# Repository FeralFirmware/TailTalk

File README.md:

# TailTalk

[![Crates.io][crates-badge]][crates-url] [![docs.rs][docs-badge]][docs-url]

[crates-badge]: https://img.shields.io/crates/v/tailtalk.svg
[crates-url]: https://crates.io/crates/tailtalk
[docs-badge]: https://img.shields.io/docsrs/tailtalk.svg
[docs-url]: https://docs.rs/tailtalk/latest/tailtalk/

TailTalk is designed as a "toolkit" for building fully userspace AppleTalk implementations on Linux, Mac OS and Windows
systems via EtherTalk or LocalTalk networks. It is built from scratch with zero dependencies on Netatalk or any kernel
drivers - All it needs is a raw socket and/or TashTalk compatible device (for LocalTalk) and patience for grumpy old computers.
It provides a complete AppleTalk stack, with multiple copies of it able to run on the same machine
at the same time.

I started this project to be able to copy files to/from my old Macs, print to LaserWriters, ImageWriters and networked StyleWriters, and be able
to write modern async software to communicate with them. Currently TailTalk only works in a routerless setup - work is in progress
to make it gracefully join router present networks but it is not yet in the mainline code.

Each part of the stack is meant to be as "zero config" as possible, just like running on a Mac of the era. Just plug it in,
launch and things should just work without any fuss.

This project is very much a work in progress prototype, so expect bugs and missing features.

## TailTalk GUI

This is the current user facing program for use with TashTalk USB. It includes an AFP server which should work with just about
every Mac that shipped with a LocalTalk port. It also can import Stuff-It archives and floppy disk images and load them in to
the share path preserving the resource forks and make them available to remote clients.

It additionally supports sharing LocalTalk capable LaserWriters, ImageWriters and StyleWriters to modern networks as AirPrint / IPP printers,
and sharing modern printers to classic Macs. The latest release can be found here:

[https://github.com/FeralFirmware/TailTalk/releases/latest](https://github.com/FeralFirmware/TailTalk/releases/latest)

## Features

Packet parsers and fully async APIs for almost all the major AppleTalk protocols.

- AppleTalk Address Resolution Protocol (AARP)
- Datagram Delivery Protocol (DDP)
- Name Binding Protocol (NBP)
- AppleTalk Transaction Protocol (ATP)
- Printer Access Protocol (PAP)
- AppleTalk Session Protocol (ASP)
- AppleTalk Filing Protocol (AFP)
- AppleTalk Data Stream Protocol

It additionally supports running with TashTalk for LocalTalk Macs.

The AARP/DDP underlay can run either in-process (the default) or in a shared
daemon, `tailtalkd`, which owns the interfaces and serves DDP sockets,
addressing, and routing rules to multiple clients over a protobuf protocol on
a Unix or UDP socket — usable from TailTalk (`TalkStack::builder().daemon_unix(..)`)
or plain C clients. See [docs/daemon-protocol.md](docs/daemon-protocol.md).

## Building

### Prerequisites

This project requires Rust 1.90 or above, which can be installed from [rustup.rs](https://rustup.rs). This should install
a matching compiler for your OS and CPU architecture by default.

This project uses [cargo-packager](github.com/crabnebula-dev/cargo-packager) for building AppImage for Linux, and App bundles
for macOS and installers for Windows. Install it with `cargo install cargo-packager`.

### Windows Only

Ensure you have the Windows MSVC prerequisites installed as specified in the [rustup book](https://rust-lang.github.io/rustup/installation/windows-msvc.html).

Windows requires the npcap SDK to be saved somewhere on your machine. It is available at [npcap.com](https://npcap.com/#download). Point a LIB environment variable to the folder where you unzipped the SDK, such as:
``` C:\npcap-sdk-1.13\Lib\x64```

### Running the build

Once the prerequisites are installed, run `cargo build --release` from the root of this repository to build everything, or for just the
TailTail GUI run `cargo build -p tailtalk-gui --release`.

After building the binaries should be located at `target/release/`.

Then run the following based on your OS:
```sh
# Linux
cargo packager --release -f appimage -p tailtalk-gui
# macOS
cargo packager --release -p tailtalk-gui
# Windows 
cargo packager --release -f nsis -p tailtalk-gui

```

The resulting bundle will be placed in dist/. 

## TashTalk USB

Quick start guide: [Setup.md](/Setup.md)

TashTalk USB uses a Silicon Labs CP210x USB-to-UART bridge (VID `10c4`, PID `ea60`). 

### Linux
The `cp210x` kernel module is likely installed already but by default the device node is only accessible by root. To grant your user
access without requiring root, create a udev rule:

```sh
echo 'SUBSYSTEM=="tty", ATTRS{idVendor}=="10c4", ATTRS{idProduct}=="ea60", TAG+="uaccess"' \
  | sudo tee /etc/udev/rules.d/99-tashtalk-usb.rules
sudo udevadm control --reload-rules && sudo udevadm trigger
```

After running these commands, unplug and re-plug the TashTalk USB device. It will appear as `/dev/ttyUSB0` (or
similar) and be accessible without root.

### Windows
Install the CP210x VCP Windows driver from 
[Silicon Labs](https://www.silabs.com/software-and-tools/usb-to-uart-bridge-vcp-drivers?tab=downloads).

Install npcap 1.88 from [npcap.com](https://npcap.com/#download)

### MacOS
macOS 11 and later includes support for the CP2102N USB chip out of the box. For 10.12 through 10.15 the driver from Silicon
Labs is required for the device to be recognised: https://www.silabs.com/software-and-tools/usb-to-uart-bridge-vcp-drivers?tab=downloads

## EtherTalk

EtherTalk is compiled into the GUI by default on macOS, where libpcap ships with the OS. On Linux and Windows it is opt-in:
build with `cargo build -p tailtalk-gui --features ethertalk` once libpcap (`libpcap-dev`) or the npcap SDK is installed.

### macOS

Packet capture and injection go through `/dev/bpf*`, which is root-only out of the box. To use EtherTalk as a regular user,
install the **ChmodBPF** package that ships inside the Wireshark disk image (or run `brew install --cask wireshark-chmodbpf`).
It creates an `access_bpf` group, hands the BPF devices to it, and adds you to the group.

Group membership only applies to new login sessions, so **log out and back in** afterwards. Until then, and if ChmodBPF is not
installed at all, the GUI hides the Ethernet Interface picker rather than offering a transport that would fail to start.

## Existing Programs
There are 4 demo programs I have written to verify the functionality of this software as I have developed it:

- [aep-echo](/examples/aep-echo/) - A simple echo program that sends an echo request to a target address and prints the response time.
- [afp-server](/examples/afp-server) - An AFP 1.0, 1.1 and 2.0 compatible AFP server. Very much a work in progress but is capable of reading and writing files to classic Mac systems. Basic directory browsing and file operations are supported.
- [nbp-lookup](/examples/nbp-lookup) - Performs an NBP lookup based on the provided request string and returns the results
- [pap-print](/examples/pap-print) - Sends a PostScript file to a PAP printer. Aimed at LaserWriters, and have only tested on my own 4/600 PS.
- [tailtalkd](/tailtalk-daemon/) - The TailTalk underlay daemon. Owns the physical AppleTalk interfaces and serves DDP sockets, addressing, and routing to client applications over a Unix/UDP socket.
- [tailtalk-gui](/examples/tailtalk-gui/) - A simple GUI for sharing a folder as a volume over EtherTalk and/or LocalTalk (via TashTalk).

All of the examples run a complete copy of the stack using a raw socket (if EtherTalk is enabled) and thus need to be run as root,
 or the appropriate setcap applied to the compiled binary (on macOS, ChmodBPF instead, see [EtherTalk](#ethertalk)). If only
 using TashTalk then this is not required.

## Testing

Beyond unit tests I have found the best way to test this software is with real hardware. My current test setup consists of:

- Linux machine running TailTalk
- PowerBook G3 running Mac OS 9.2 via Ethernet
- LaserWriter 4/600 PS via AsanteTalk
- Color StyleWriter 2200 via EtherTalk adapter
- ImageWriter II with the LocalTalk Option Card
- Macintosh SE/30 running System 7.1 via AsanteTalk
- Macintosh Classic running System 6.0.8 via AsanteTalk

### AsanteTalk

When the AsanteTalk is first powered on it "listens" for incoming packets on the Ethernet
side before choosing what EtherTalk phase to operate under. If it doesn't see any EtherTalk Phase 2 packets it will default to
Phase 1. TailTalk supports Phase 1 and this works just fine for LaserWriters, NBP and some basic operations but does
not work with AFP (The Mac will discover the AFP TailTalk server but our responses appear to be dropped).

## Contributing

I'd love to see this project grow into something that can be used to build more complete AppleTalk implementations. All contributions 
are welcome, but please open an issue first to discuss the changes you'd like to make. Additionally Pull Requests should mention what 
systems the change was verified against. This project has made me realise how quirky old systems are.

## License

This project is licensed under the GNU General Public License v3.0 - see the [LICENSE](LICENSE) file for details.

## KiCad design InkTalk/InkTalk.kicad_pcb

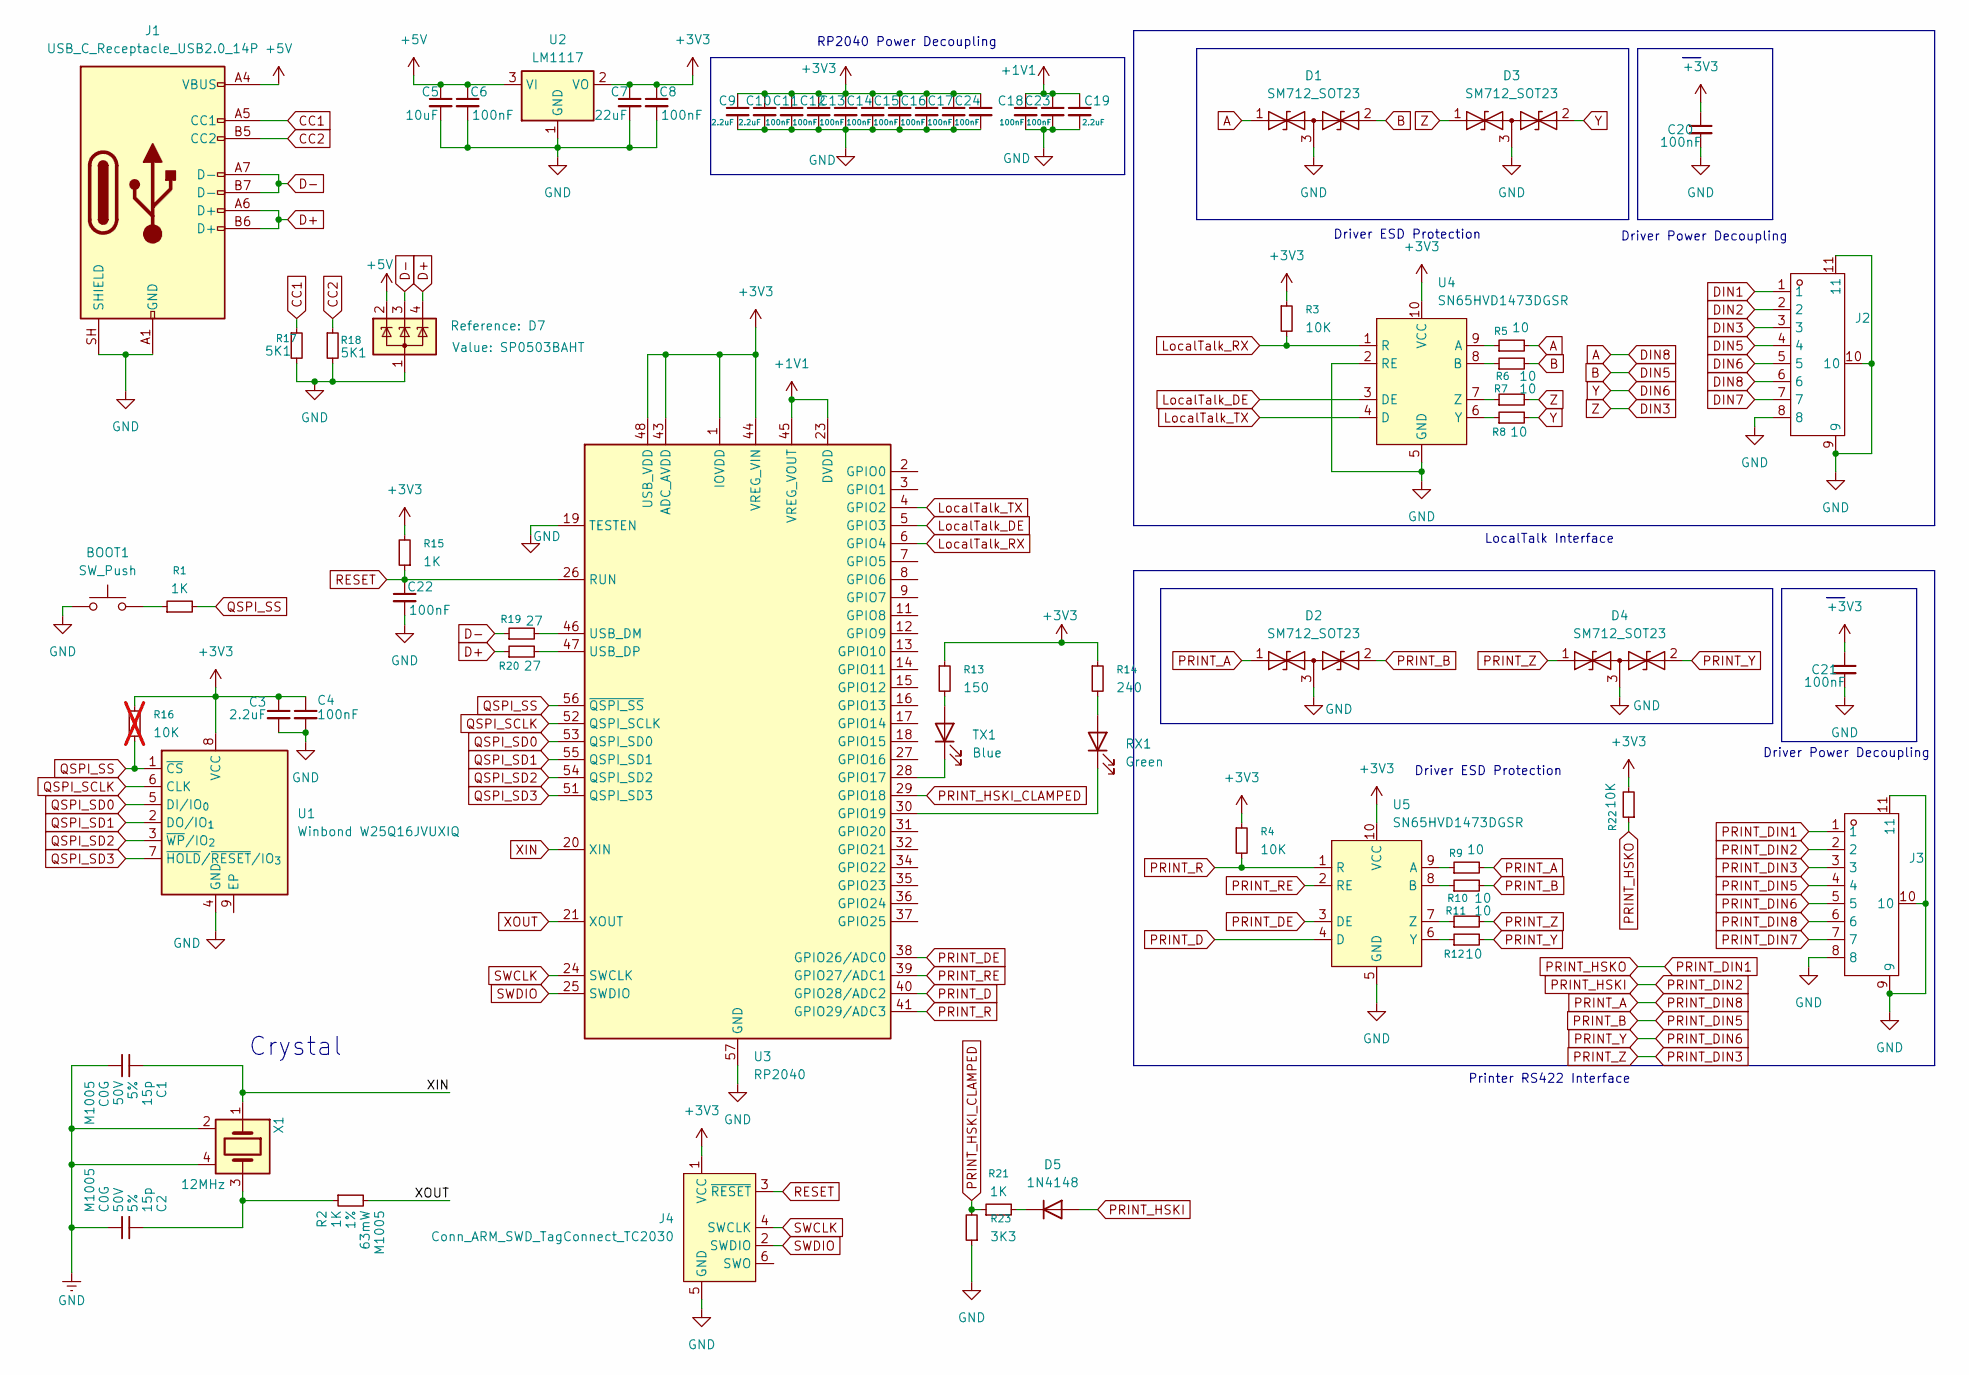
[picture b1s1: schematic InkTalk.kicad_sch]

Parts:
BOOT1: SW_Push; SW_SPST_TS-1088-xR020
C1, C2: 15p; C_0402_1005Metric; voltage 50V; tolerance 5%; part_uid RP-01C89W-LLY9XV
C3, C9, C10, C19: 2.2uF; C_0402_1005Metric
C4, C6, C8, C11, C12, C13, C14, C15, C16, C17, C18, C22, C23, C24: 100nF; C_0402_1005Metric
C5: 10uF; C_0603_1608Metric
C7: 22uF; C_0603_1608Metric
C20, C21: 100nF; C_0402_1005Metric; LCSC C14663
D1, D2, D3, D4: SM712_SOT23; SOT-23; LCSC C404012
D5: 1N4148; D_SOD-523
D7: SP0503BAHT; SOT-143; LCSC C41364459
J1: USB_C_Receptacle_USB2.0_14P; USB_C_Receptacle_HRO_TYPE-C-31-M-12
J2, J3: CONN-TH_DIN-802; Manufacturer Part DIN-802; LCSC C41409494
J4: Conn_ARM_SWD_TagConnect_TC2030; Tag-Connect_TC2030-IDC-NL_2x03_P1.27mm_Vertical
R1, R15: 1K; R_0402_1005Metric
R2: 1K; R_0402_1005Metric; tolerance 1%; voltage 50V; part_uid RP-019A1P-4Z6ZWY
R3, R4: 10K; R_0402_1005Metric; LCSC C25804
R5, R6, R7, R8, R9, R10, R11, R12: 10; R_0402_1005Metric; LCSC C22859
R13: 150; R_0402_1005Metric; LCSC C23025
R14: 240; R_0402_1005Metric; LCSC C23350
R16: 10K; R_0402_1005Metric; not fitted
R17, R18: 5K1; R_0402_1005Metric; LCSC C23186
R19, R20: 27; R_0402_1005Metric
R21: 1K; R_0402_1005Metric; LCSC C25804
R22: 10K; R_0402_1005Metric; LCSC C22859
R23: 3K3; R_0402_1005Metric; LCSC C25804
RX1: Green; LED_0603_1608Metric; LCSC C2289
TX1: Blue; LED_0603_1608Metric; LCSC C51933294
U1: Winbond W25Q16JVUXIQ; Winbond_USON-8-1EP_3x2mm_P0.5mm_EP0.2x1.6mm
U2: LM1117; SOT-23
U3: RP2040; QFN-56-1EP_7x7mm_P0.4mm_EP3.2x3.2mm
U4, U5: SN65HVD1473DGSR; MSOP-10_3x3mm_P0.5mm; LCSC C2863381
X1: 12MHz; Crystal_SMD_Abracon_ABM8AIG-4Pin_3.2x2.5mm; tolerance 30ppm; part_uid RP-01G8X7-GS352B

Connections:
+1V1: C18.1, C19.1, C23.1, U3.23 (DVDD), U3.45 (VREG_VOUT), U3.50 (DVDD)
+3V3: C3.1, C4.1, C7.1, C8.1, C9.1, C10.1, C11.1, C12.1, C13.1, C14.1, C15.1, C16.1, C17.1, C20.1, C21.1, C24.1, J4.1 (VCC), R3.1, R4.1, R13.1, R14.1, R15.2, R16.2, R22.2, U1.8 (VCC), U2.2 (VO), U3.1 (IOVDD), U3.10 (IOVDD), U3.22 (IOVDD), U3.33 (IOVDD), U3.42 (IOVDD), U3.43 (ADC_AVDD), U3.44 (VREG_VIN), U3.48 (USB_VDD), U3.49 (IOVDD), U4.10 (VCC), U5.10 (VCC)
+5V: C5.1, C6.1, D7.2 (K), J1.A4 (VBUS), J1.A9 (VBUS), J1.B4 (VBUS), J1.B9 (VBUS), U2.3 (VI)
A: D1.1 (A1), J2.6, R5.2
B: D1.2 (A2), J2.4, R6.2
CC1: J1.A5 (CC1), R17.1
CC2: J1.B5 (CC2), R18.1
D+: D7.4 (K), J1.A6 (D+), J1.B6 (D+), R20.1
D-: D7.3 (K), J1.A7 (D-), J1.B7 (D-), R19.1
DIN1: J2.1
DIN2: J2.2
DIN3: D3.1 (A1), J2.3, R7.2
DIN6: D3.2 (A2), J2.5, R8.2
DIN7: J2.7
GND: BOOT1.1, C1.2, C2.2, C3.2, C4.2, C5.2, C6.2, C7.2, C8.2, C9.2, C10.2, C11.2, C12.2, C13.2, C14.2, C15.2, C16.2, C17.2, C18.2, C19.2, C20.2, C21.2, C22.2, C23.2, C24.2, D1.3 (common), D2.3 (common), D3.3 (common), D4.3 (common), D7.1 (A), J1.A1 (GND), J1.A12 (GND), J1.B1 (GND), J1.B12 (GND), J1.SH (SHIELD), J2.8, J2.9, J2.10, J2.11, J3.8, J3.9, J3.10, J3.11, J4.5 (GND), R17.2, R18.2, R23.1, U1.4 (GND), U2.1 (GND), U3.19 (TESTEN), U3.57 (GND), U4.2 (RE), U4.5 (GND), U5.5 (GND), X1.2, X1.4
LocalTalk_DE: U3.5 (GPIO3), U4.3 (DE)
LocalTalk_RX: R3.2, U3.6 (GPIO4), U4.1 (R)
LocalTalk_TX: U3.4 (GPIO2), U4.4 (D)
unnamed: BOOT1.2, R1.1
unnamed: C2.1, R2.1, X1.3
unnamed: D5.1 (K), R21.2
unnamed: R14.2, RX1.2 (A)
unnamed: RX1.1 (K), U3.30 (GPIO19)
unnamed: R13.2, TX1.2 (A)
unnamed: TX1.1 (K), U3.28 (GPIO17)
unnamed: R19.2, U3.46 (USB_DM)
unnamed: R20.2, U3.47 (USB_DP)
unnamed: R5.1, U4.9 (A)
unnamed: R6.1, U4.8 (B)
unnamed: R8.1, U4.6 (Y)
unnamed: R7.1, U4.7 (Z)
unnamed: R9.1, U5.9 (A)
unnamed: R10.1, U5.8 (B)
unnamed: R12.1, U5.6 (Y)
unnamed: R11.1, U5.7 (Z)
PRINT_A: D2.1 (A1), J3.6, R9.2
PRINT_B: D2.2 (A2), J3.4, R10.2
PRINT_D: U3.40 (GPIO28/ADC2), U5.4 (D)
PRINT_DE: U3.38 (GPIO26/ADC0), U5.3 (DE)
PRINT_DIN1: J3.1, R22.1
PRINT_DIN2: D5.2 (A), J3.2
PRINT_DIN3: D4.1 (A1), J3.3, R11.2
PRINT_DIN6: D4.2 (A2), J3.5, R12.2
PRINT_DIN7: J3.7
PRINT_HSKI_CLAMPED: R21.1, R23.2, U3.29 (GPIO18)
PRINT_R: R4.2, U3.41 (GPIO29/ADC3), U5.1 (R)
PRINT_RE: U3.39 (GPIO27/ADC1), U5.2 (RE)
QSPI_SCLK: U1.6 (CLK), U3.52 (QSPI_SCLK)
QSPI_SD0: U1.5 (DI/IO_{0}), U3.53 (QSPI_SD0)
QSPI_SD1: U1.2 (DO/IO_{1}), U3.55 (QSPI_SD1)
QSPI_SD2: U1.3 (~WP/IO_{2}), U3.54 (QSPI_SD2)
QSPI_SD3: U1.7 (~HOLD/~RESET/IO_{3}), U3.51 (QSPI_SD3)
QSPI_SS: R1.2, R16.1, U1.1 (~CS), U3.56 (~QSPI_SS)
RESET: C22.1, J4.3 (~RESET), R15.1, U3.26 (RUN)
SWCLK: J4.4 (SWCLK), U3.24 (SWCLK)
SWDIO: J4.2 (SWDIO), U3.25 (SWDIO)
XIN: C1.1, U3.20 (XIN), X1.1
XOUT: R2.2, U3.21 (XOUT)

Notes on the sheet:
LocalTalk Interface
Driver ESD Protection
Printer RS422 Interface
Driver Power Decoupling
RP2040 Power Decoupling
Crystal

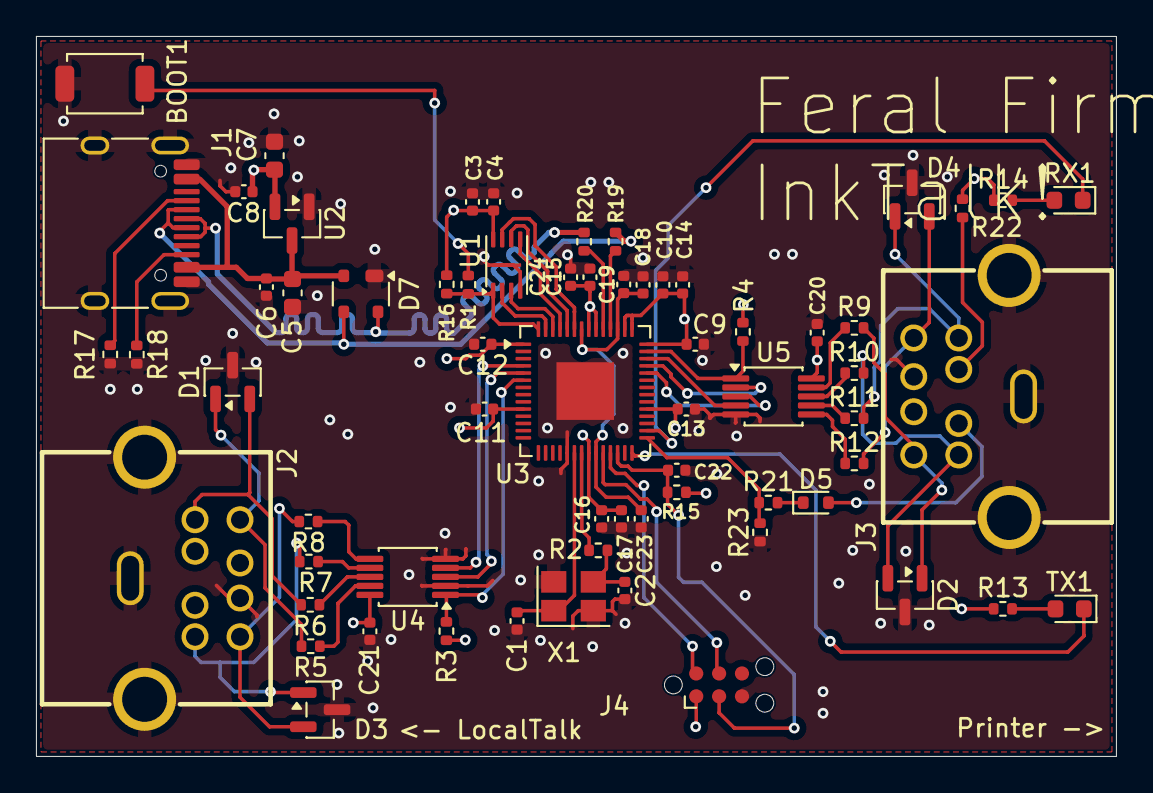
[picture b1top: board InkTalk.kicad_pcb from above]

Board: 4 copper layers, 60.0 x 40.0 mm, 66 parts (0 on the bottom side), 54 nets.

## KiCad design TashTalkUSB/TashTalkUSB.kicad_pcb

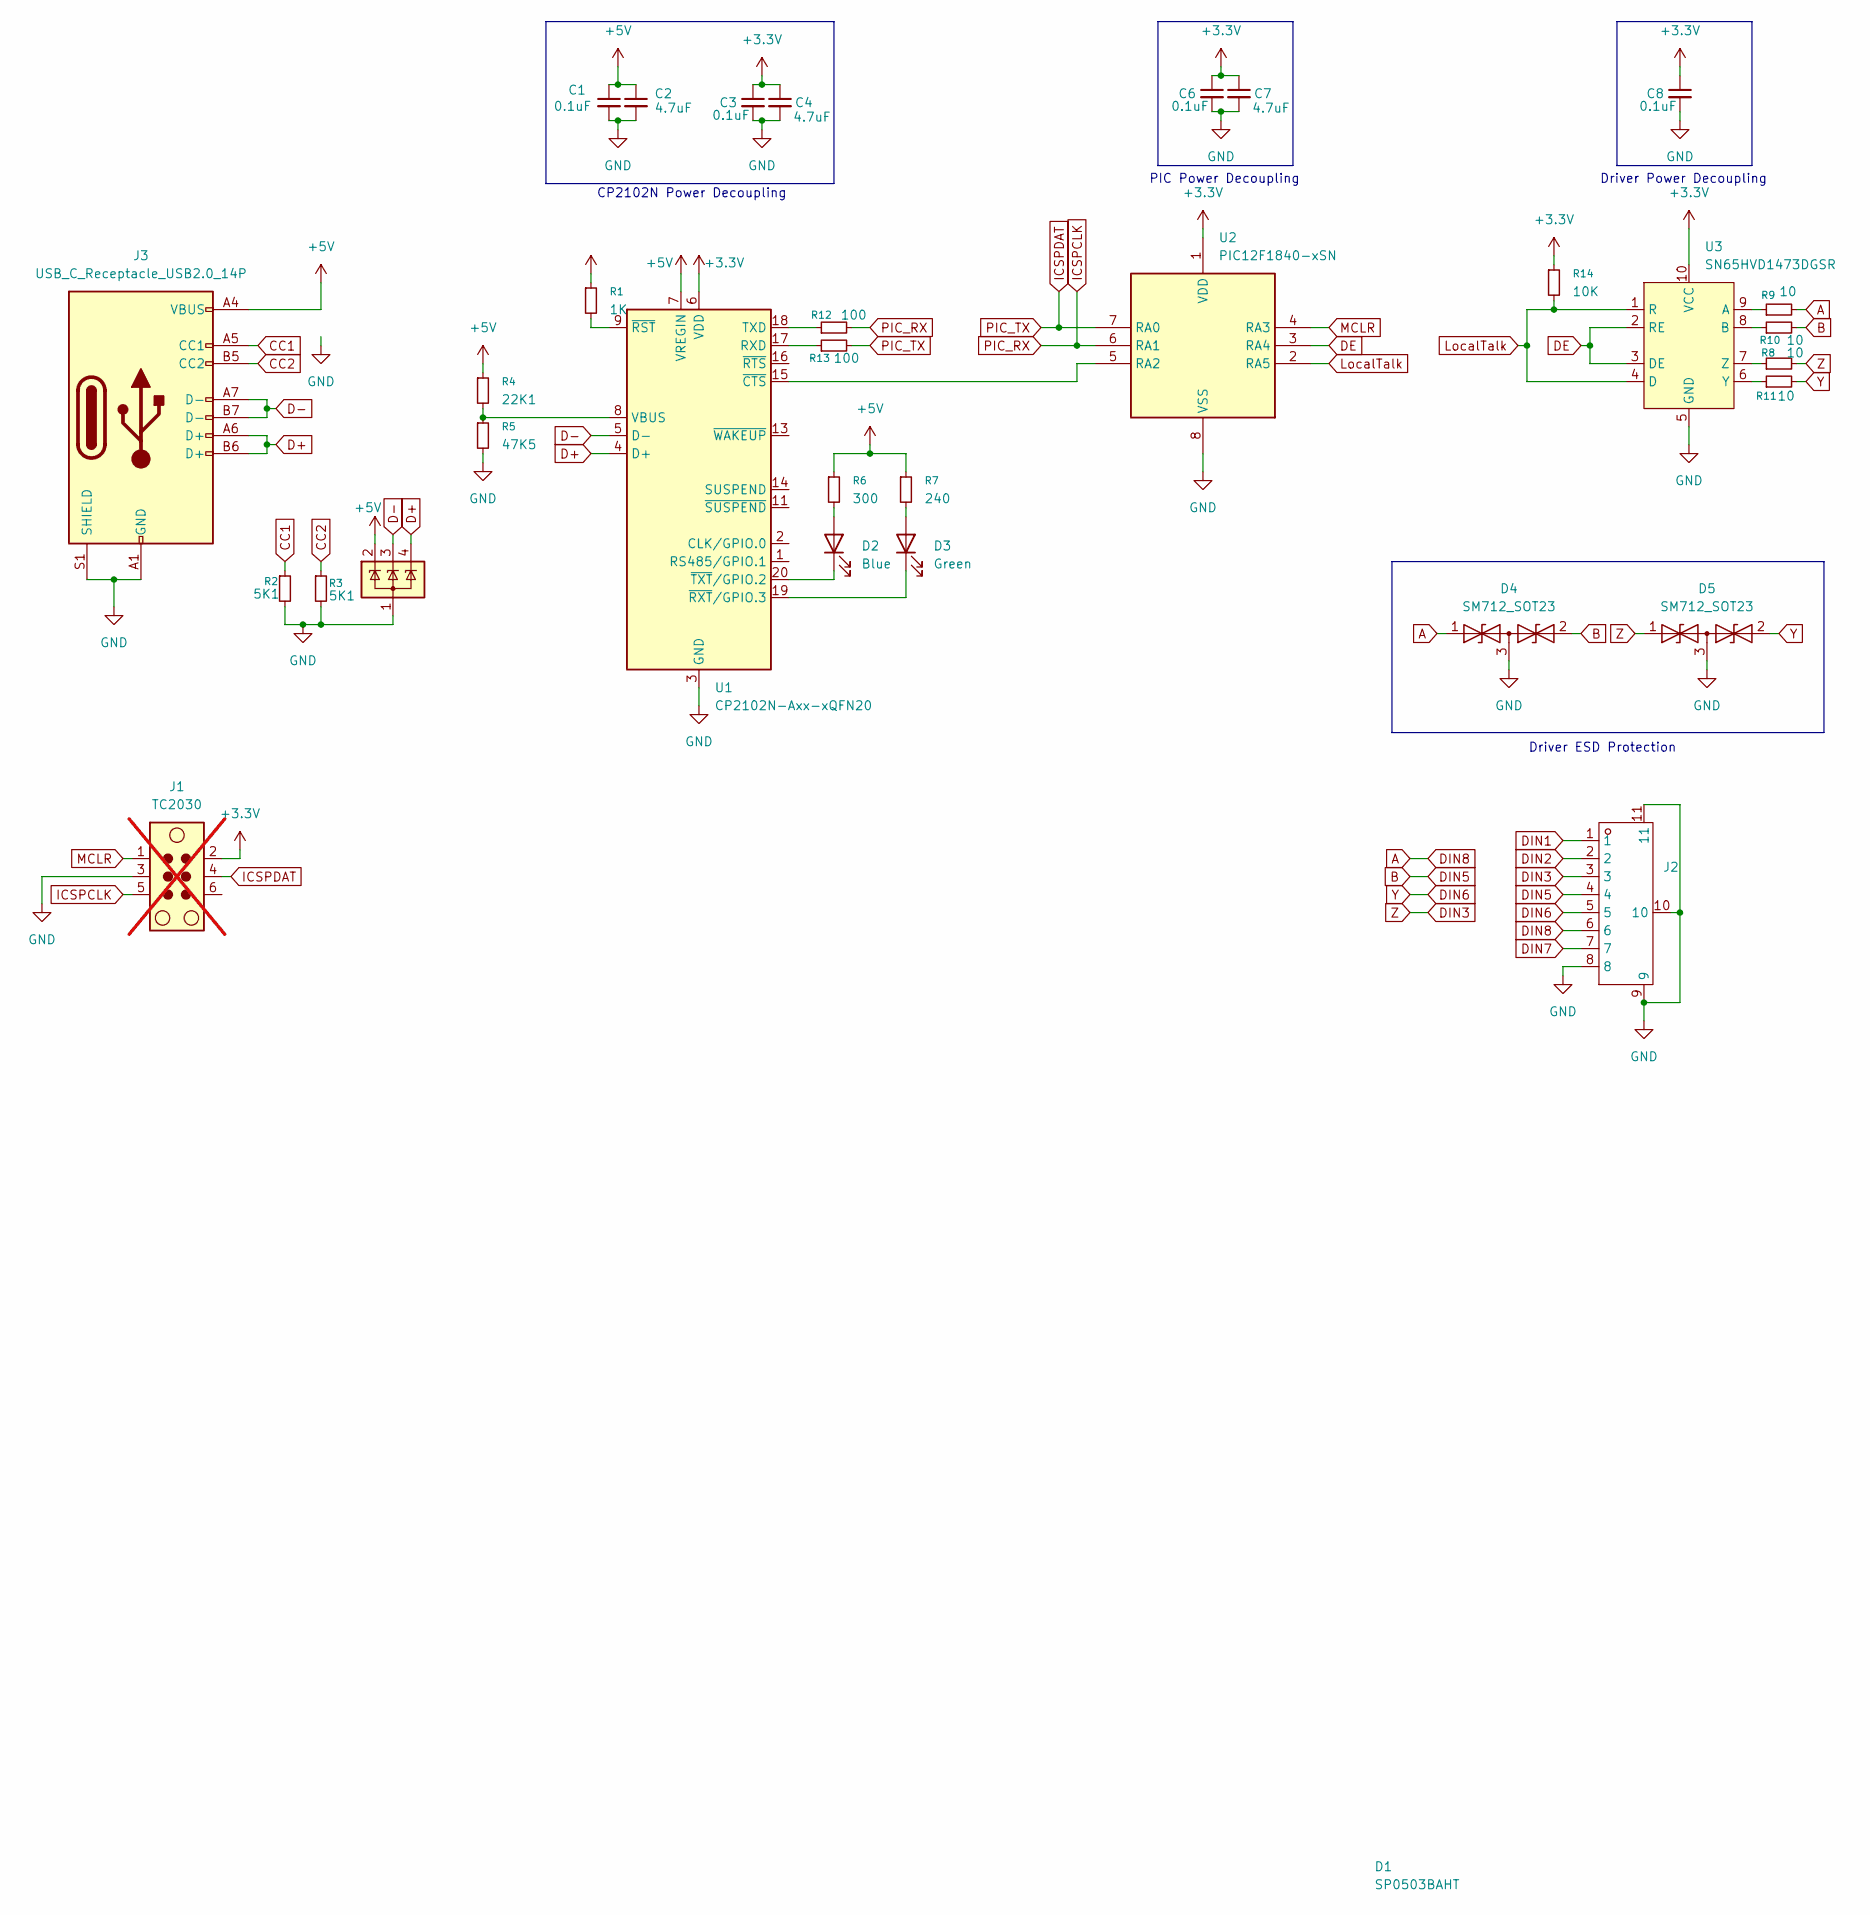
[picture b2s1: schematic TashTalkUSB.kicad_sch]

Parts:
C1, C3, C6, C8: 0.1uF; C_0603_1608Metric; LCSC C14663
C2, C4, C7: 4.7uF; C_0603_1608Metric; LCSC C19666
D1: SP0503BAHT; SOT-143; LCSC C41364459
D2: Blue; LED_0603_1608Metric; LCSC C51933294
D3: Green; LED_0603_1608Metric; LCSC C2986048
D4, D5: SM712_SOT23; SOT-23; LCSC C404012
J1: TC2030; Tag-Connect_TC2030-IDC-NL_2x03_P1.27mm_Vertical; LCSC N/A; not fitted
J2: CONN-TH_DIN-802; Manufacturer Part DIN-802; LCSC C41409494
J3: USB_C_Receptacle_USB2.0_14P; USB_C_Receptacle_HRO_TYPE-C-31-M-12; LCSC C165948
R1: 1K; R_0603_1608Metric; LCSC C21190
R2, R3: 5K1; R_0603_1608Metric; LCSC C23186
R4: 22K1; R_0603_1608Metric; LCSC C31850
R5: 47K5; R_0603_1608Metric; LCSC C25819
R6: 300; R_0603_1608Metric; LCSC C23025
R7: 240; R_0603_1608Metric; LCSC C23350
R8, R9, R10, R11: 10; R_0603_1608Metric; LCSC C22859
R12, R13: 100; R_0603_1608Metric; LCSC C22775
R14: 10K; R_0603_1608Metric; LCSC C25804
U1: CP2102N-Axx-xQFN20; SiliconLabs_QFN-20-1EP_3x3mm_P0.5mm_EP1.8x1.8mm; LCSC C969913
U2: PIC12F1840-xSN; SOIC-8_3.9x4.9mm_P1.27mm; LCSC C39594
U3: SN65HVD1473DGSR; MSOP-10_3x3mm_P0.5mm; LCSC C2863381

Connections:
+3.3V: C3.1, C4.1, C6.1, C7.1, C8.1, J1.2, R1.1, R14.1, U1.6 (VDD), U2.1 (VDD), U3.10 (VCC)
+5V: C1.1, C2.1, D1.2 (K), J3.A4 (VBUS), J3.A9 (VBUS), J3.B4 (VBUS), J3.B9 (VBUS), R4.1, R6.1, R7.1, U1.7 (VREGIN)
A: D4.1 (A1), J2.6, R9.2
B: D4.2 (A2), J2.4, R10.2
CC1: J3.A5 (CC1), R2.1
CC2: J3.B5 (CC2), R3.1
D+: D1.4 (K), J3.A6 (D+), J3.B6 (D+), U1.4 (D+)
D-: D1.3 (K), J3.A7 (D-), J3.B7 (D-), U1.5 (D-)
DE: U2.3 (RA4), U3.2 (RE), U3.3 (DE)
DIN1: J2.1
DIN2: J2.2
DIN3: D5.1 (A1), J2.3, R8.2
DIN6: D5.2 (A2), J2.5, R11.2
DIN7: J2.7
GND: C1.2, C2.2, C3.2, C4.2, C6.2, C7.2, C8.2, D1.1 (A), D4.3 (common), D5.3 (common), J1.3, J2.8, J2.9, J2.10, J2.11, J3.A1 (GND), J3.A12 (GND), J3.B1 (GND), J3.B12 (GND), J3.S1 (SHIELD), R2.2, R3.2, R5.2, U1.3 (GND), U1.12 (GND), U1.21 (GND), U2.8 (VSS), U3.5 (GND)
ICSPCLK: J1.5, R12.2, U2.6 (RA1)
ICSPDAT: J1.4, R13.2, U2.7 (RA0)
LocalTalk: R14.2, U2.2 (RA5), U3.1 (R), U3.4 (D)
MCLR: J1.1, U2.4 (RA3)
unnamed: D2.2 (A), R6.2
unnamed: D2.1 (K), U1.20 (~TXT/GPIO.2)
unnamed: D3.2 (A), R7.2
unnamed: D3.1 (K), U1.19 (~RXT/GPIO.3)
unnamed: R13.1, U1.17 (RXD)
unnamed: R12.1, U1.18 (TXD)
unnamed: R4.2, R5.1, U1.8 (VBUS)
unnamed: U1.15 (~CTS), U2.5 (RA2)
unnamed: R1.2, U1.9 (~RST)
unnamed: R9.1, U3.9 (A)
unnamed: R10.1, U3.8 (B)
unnamed: R11.1, U3.6 (Y)
unnamed: R8.1, U3.7 (Z)

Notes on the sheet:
CP2102N Power Decoupling
Driver ESD Protection
PIC Power Decoupling
Driver Power Decoupling

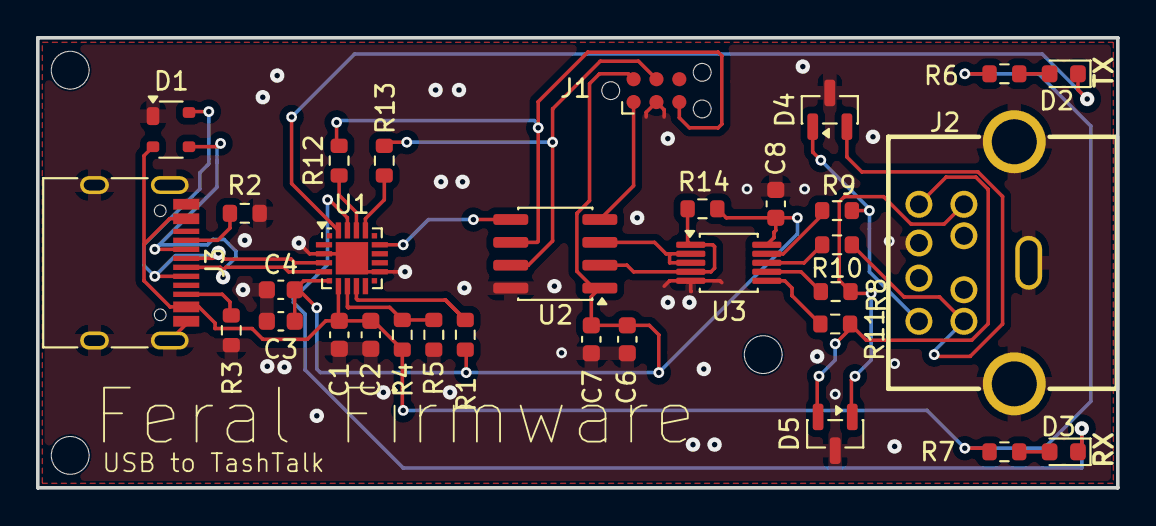
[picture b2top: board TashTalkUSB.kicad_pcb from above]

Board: 2 copper layers, 60.0 x 25.0 mm, 32 parts (0 on the bottom side), 29 nets.

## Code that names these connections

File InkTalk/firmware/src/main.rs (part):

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//! | GPIO | Net | Function |
//! |---|---|---|
//! | GP2  | `LocalTalk_TX`         | PIO0 SM0 OUT -> U4 D |
//! | GP3  | `LocalTalk_DE`         | software GPIO -> U4 DE |
//! | GP4  | `LocalTalk_RX`         | PIO1 SM0 JMP PIN <- U4 R |
//! | GP6/7| (unconnected)          | DBG0/DBG1 scope outputs |
//! | GP17 | `Net-(TX1-K)`          | TX1 blue LED, active low |
//! | GP18 | `PRINT_HSKI_CLAMPED`   | UART0 CTS <- printer HSKi, inverted in the pad. A Colour StyleWriter's fast clock for PIO0, not inverted |
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    let cfg = config::load(&mut flash);
    info!("config: role={} baud={}", cfg.role as u8, cfg.baud);

    // ── LocalTalk PHY (configures PIO + pins, drops handles) ────────
    let pio0_spare = localtalk::phy::init_phy(
        p.PIO0,
        localtalk::phy::Pio0Irqs {},
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
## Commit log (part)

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2026-02-28 Add MacString helper for reading MacRoman PascalStrings and use new Rust 1.93 as_array slice method versus ugly try_into.
2026-02-28 Implement calls for Get/Set on the root AFP directory (ID 1)
2026-03-01 Add AsanteTalk note to README
2026-03-01 Document known issues at this point
2026-03-16 Add TashTalk support, start porting lpstyl to Rust, make ADSP actually almost work
2026-04-05 Add prototype USB-to-TashTalk schem/pcb
2026-04-11 Swap to builder API to allow TashTalk only setups. Refactor ADSP code.
2026-04-12 Fix AFP TID wrapping. Remove AFP instability note as large transfers seem stable now
2026-04-13 Add start of GUI for file sharing
2026-04-13 Switch to libpcap and tweak xattr for macOS support
2026-04-19 Fix AFP Commands, add TashTalk CRC gen, start on resource fork support
    * LocalTalk CRC now computed in host software rather than relying on TashTalk firmware, with a new lt_crc helper; CRC generation/checking are user-configurable instead of hardcoded
    * ASP tickles re-enabled; ATP gains a fire-and-forget ALO send path for this
    * Resource forks supported via .tailtalk/rsrc/ sidecar files; RESOURCE_FORK_LENGTH now reports actual size
    * BACKUP_DATE returns the AFP "never backed up" sentinel (0x80000000) instead of mtime
    * Volume mtime now read from the filesystem instead of returning creation time
    * set_node_parms fixed to handle both files and directories, not just directories
2026-04-19 Update PCB and schematic with fixed mini-DIN 8 pinout
2026-04-19 Unify deps with cargo-rail, fix EtherTalk filtering
2026-04-23 TashTalk 0.2.0 release
2026-04-25 Add single stack creation/entry point and update examples
2026-04-25 Fix parsing of FPSetFileDirParms
2026-05-01 TashTalk USB Rev 2
2026-05-01 Remove old PCB CSVs
2026-05-01 Refactor AFP commands out of server.s and in to tailtalk-packets Add support for FPMoveAndRename Start adding unit tests for problematic Mac shutdown/unmount seq
2026-05-02 AFP: Implement FPRename
2026-05-11 CI: Add first pass at build + release upload
2026-05-11 Fix failing AFP and doc tests
2026-05-24 Per-interface addressing, revert LocalTalk AARP, and clippy fixes
    Split DDP, NBP, and TalkStack into separate et_addressing /
    lt_addressing handles so each interface has its own AppleTalk
    address. Reverts the HardwareAddress enum from AarpPacket — LocalTalk
    uses LLAP ENQ/ACK for node assignment, not AARP. try_lookup now
    routes network 0 directly to Node::LocalTalk by address invariant
    rather than by handle type. AddressingHandle.cache is private behind
2026-05-24 AFP: Use pure-magic crate for determining file types
    Swaps from the primary mechanism being extensions to determine file types
    to pure-magic, which will try and see what a file is versus just blindly
    trusting the extension like Windows. The fallbacks are still present
    if pure-magic cannot recognise any matches.
    This should allow things like plain text files without an extension to
    now automatically open in SimpleText.
2026-05-24 GUI: Add new file menu option to inspect and set finder info
    Adds a new context menu button to view the current finder info
    (specifically the creator / file type) and optionally set it. This
    can be used to override the defaults set by TailTalk or a previous run.
2026-05-24 Fix resource fork identification for APPL files
2026-05-24 AFP+GUI: Use a defined type for Finder Info, async-ify GUI
    Moves our code off of hand rolling and unrolling the 32-byte finder
    info and instead to a real type that we can serialise and deserialise to.
    Updated all call sites to use this new one.
    Additionally async-ifies our GUI versus the awkward scattered thread
    creation everywhere. As part of this our TailTalk side code has shedded
    the sync FS calls in favour of Tokio async ones.
2026-05-24 GUI: Update layout
    Based on recommendations from Iantm from 68KMLA this commit tweaks
    our GUI's layout to have categorised sections. Additionally makes it
    so our pcap button enables and disables the file browser versus
    hiding and showing it.
2026-05-25 Add /dist, .DS_Store to .gitignore
2026-05-25 resolve_resource_fork_path(): use tokio for async I/O, and return resource fork length
2026-05-26 ci: Add Windows builds
    Our GUI and TailTalk _should_ build on Windows, but I honestly have
    no idea if it works yet as I do not own a Windows machine. This
    commit adds the CI framework for now which we will use to test and
    ideally produce runnable tailtalk gui exe files which we can give
    to end users for verification before merging.
2026-05-27 docs: Add TashTalk USB and GUI quick start guide
    Adds a quicck start guide for using the TashTalk USB device with
    the GUI and how to mount the volume shared with it.
    Additionally updates our file mapping for StuffIt SEA files,
    and BinHex HQX files.
2026-05-27 GUI: Add "Import HFS disk image" button
    In the same vein as the Stuff-It import added, this commit
    adds the option to import a raw HFS disk image, or a Disk Copy 4.2
    image. The image will then be parsed and all files and folders
    (including data+resource forks, icons and desktop entries) will be
    copied in to a matching folder name in the selected share path.
    To support this I have put together a rather simple little HFS read only
2026-05-28 Mac: Use native resource forks by default
    Swaps macOS clients for our AFP server to using native resource
    forks versus sidecar files. There's no real need to use sidecars
    on an OS that natively supports them. For users upgrading from
    previous versions we will still fallback to loading from sidecars.
2026-06-02 AFP: Add name mangling support
    Coming from a report from Iesca on 68KMLA it was found that file names
    exceeding the AFP limit could be sent to clients and appeared to work
    OK, but would cause silent memory corruption on the classic Mac. It
    would then cause rather odd failures (In their case, the IIfx would freeze
    when trying to copy a file. On my 512K it could copy OK, but doing a Get Info
    on any folder containing along file name would cause an address error).
2026-06-02 Add instructions for windows prerequisites and building
2026-06-03 ci: Add Windows builds
    Enables builds, tests and releases for Windows given that TailTalk (and
    by extension the GUI) work just fine on the platform after testing by
    a 68KMLA user. Thank you @nutzman!
    Tested-by: Josh Nutzman <josh@tradewinddatascience.com>
2026-06-06 ci: Add separate x86_64 image for older Macs
    Building universal binaries raises the minimum macOS version to the
    higher of the two binaries, which in our case is 11.0 for Apple Silicon.
    This present our program from working on Sierra even though it should
    be compatible. To make this work we will still produce a universal
    app, but also an x86_64 specific one which will have a base requirement
    of 10.12 or above.
2026-06-06 EtherTalk: Fix broadcast addressing for Phase 2 and NBP
    We were using FF:FF:FF:FF:FF:FF for all AppleTalk broadcast traffic
    regardless of phase. EtherTalk Phase 2 requires 09:00:07:FF:FF:FF for
    both AARP and DDP broadcasts.
    Addressing::spawn now takes an explicit phase, used to select the
    correct broadcast MAC for AARP probes and requests. try_lookup now
    resolves node 255 before checking network 0, so {0, 255} resolves
2026-06-09 Update README with macOS driver instructions
    Added macOS support information for CP2102N USB chip.
2026-06-09 Revise driver notes reference for OS compatibility
    Updated driver notes link for Windows and Mac OS users.
2026-06-13 GUI: Swap to stuffit-rs fork
    Swaps to my stuffit-rs fork as it has a bugfix that the
    maintainer has yet to merge in upstream. Hopefully will only be
    temporary.
2026-06-13 GUI: Add "Open Log Directory" button and log to file for Linux/Windows
    Tweaks our logging behaviour so when launched on Linux and macOS but
    not in a terminal (i.e via the packaged app) we will log to the default
    log directory for user data. On Windows where GUI programs aren't terminal
    programs it always logs to a file.
    As well we now have a simple "Open Log Directory" button to fetch the log
    files the program produced. This should help aid in debugging for end
2026-06-14 TailTalk: Gate Pcap usage behind ethertalk flag
    Refactors our code base so only if the "ethertalk" feature flag is set
    do we actually pull in the pcap crate. This makes it so our packages
    published on GitHub which has this feature disabled does not actually
    require libpcap to be bundled (for macOS / Linux) or installed (for Windows).
    Additionally bumps our deps to the latest versions and some minor changes
    associated with the crate bumps.
2026-06-18 PAP: Fix protocol bugs and add pap-print query subcommands
    Fixes several correctness issues found while getting printing working:
    the Data (TResp) packet had sequence number echoed into byte 3 when
    the spec says byte 3 is always 0; SendData (TReq) had the sequence
    number in only byte 3 when it is a big-endian u16 spanning bytes 2–3.
    CloseConn was being sent to the NBP listening socket instead of the
    per-connection socket from OpenConnReply. The PAP client was also
2026-06-19 Fix protocol correctness bugs in NBP, DDP, ATP, and ASP
    NBP's fully_qualified() was rejecting zone "*", which is the standard
    AppleTalk registration convention for "my current zone" (resolved by the
    router). The check now only validates object and type for wildcard
    characters. The associated error message for a misplaced ':' was also
    backwards — it said "before @" when the condition fires when ':' is
    found after '@'.
2026-06-20 GUI: Add binhex import option, consolidate import methods
    Pulls in binhex-rs so we can import binhex'd files just like Netatalk.
    As part of this we also consolidate all the import buttons in to a single
    one that offers changing the archive type in the file picker.
2026-06-21 Demo broker for Netatalk
2026-06-25 Stack: Add route table for multi-segment AppleTalk networking
    Introduces a RouteTable that maps DDP cable ranges to next-hop routers
    (RTMP) and zone names to cable ranges (ZIP), wired into both DDP outbound
    dispatch and NBP LkUp handling. This is the groundwork needed to operate
    on networks with a router or bridge present, such as a LocalTalk-to-
    Ethernet bridge like a Farallon EtherWave or AsanteTalk.
    With no routes programmed behaviour is identical to before. Routes are
2026-06-25 GUI: Add LaserWriter printing bridge mode
    Adds a new little feature to our GUI that when checked on the main screen will
    periodically scan for LaserWriters on the local network after the server starts.
    If one is found, we will query the printer for its capabilities and expose it as
    an AirPrint / IPP printer, making it usable by modern devices (i.e iPhones, the
    host system itself, and anything that can talk IPP).
    It is _super_ hacky at this point. I made it do some pre-rasterisation down to 1-bit
2026-06-28 GUI+AFP: Use shellexpand for ~ expansion, return volume errors to user
    Imports the shellexpand crate so that way manually entered paths will
    be able to use ~/ as part of the pathname. Previously we would end up
    resolving this to $CWD/~/ which when used with the macOS app version
    would give a confusing error.
    Additionally this error was only visible in the logs - when a Mac would
    try and connect we'd return a server unavailable error message and it
2026-06-29 Bump tar from 0.4.45 to 0.4.46
    Bumps [tar](https://github.com/composefs/tar-rs) from 0.4.45 to 0.4.46.
    - [Release notes](https://github.com/composefs/tar-rs/releases)
    - [Commits](https://github.com/composefs/tar-rs/compare/0.4.45...0.4.46)
    ---
    updated-dependencies:
    - dependency-name: tar
